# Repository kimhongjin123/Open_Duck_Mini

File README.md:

# Open Duck Mini v2

<table>
  <tr>
    <td> </td>
    <td> </td>
    <td> </td>
   </tr> 
</table>

## Fork addition: MiniDuck IO Shield

This fork adds a custom Raspberry Pi Zero 2 W I/O shield designed for the Open Duck Mini prototype. The addition includes the complete KiCad 9 project, connector and GPIO mapping, BOM, schematic PDF, prototype manufacturing outputs, photos, and a hardware demonstration video.

**[Open the MiniDuck IO Shield documentation](hardware/miniduck-io-shield/README.md)**

> [!IMPORTANT]
> This shield is a community hardware addition maintained in this fork; it is not part of the upstream Open Duck Mini design. Review the documented prototype warnings before fabrication.

We are making a miniature version of the BDX Droid by Disney. It is about 42 centimeters tall with its legs extended.
The full BOM cost should be under $400 !

This repo is kind of a hub where we centralize all resources related to this project. This is a working repo, so there are a lot of undocumented scripts :) We'll try to clean things up at some point.

# State of sim2real

https://github.com/user-attachments/assets/58721d0f-2f95-4088-8900-a5d02f41bba7

https://github.com/user-attachments/assets/4129974a-9d97-4651-9474-c078043bb182

https://github.com/user-attachments/assets/a0afcd38-15d8-40c6-8171-a619107406b8

# Updates

> Update 02/04/2024: You can try two policies we trained : [this one](BEST_WALK_ONNX.onnx) and [this one](BEST_WALK_ONNX_2.onnx)
> Run with the following arguments :
> python v2_rl_walk_mujoco.py --onnx_model_path ~/BEST_WALK_ONNX_2.onnx

> Update 15/03/2025: join our discord server to get help or show us your duck :) https://discord.gg/UtJZsgfQGe

> Update 07/02/2025: Big progress on sim2real, see videos above :)

> Update 24/02/2025: Working hard on sim2real ! 

> Update 07/02/2025 : We are writing documentation on the go, but the design and BOM should not change drastically. Still missing the "expression" features, but they can be added after building the robot!

> Update 22/01/2025 : The mechanical design is pretty much finalized (fixing some mistakes here and there). The current version does not include all the "expression" features we want to include in the final robot (LEDs for the eyes, a camera, a speaker and a microphone). We are now working on making it walk with reinforcement learning !

# Community 

Join our discord community ! https://discord.gg/UtJZsgfQGe

# CAD

https://cad.onshape.com/documents/64074dfcfa379b37d8a47762/w/3650ab4221e215a4f65eb7fe/e/0505c262d882183a25049d05

See [this document](docs/prepare_robot.md) for getting from a onshape design to a simulated robot in MuJoCo (Warning, outdated. Has not been updated in a while)

# RL stuff

We are switching to Mujoco Playground, see this [repo](https://github.com/apirrone/Open_Duck_Playground)

https://github.com/user-attachments/assets/037a1790-7ac1-4140-b154-2c901d20d5f5

## Reference motion generation for imitation learning 

https://github.com/user-attachments/assets/4cb52e17-99a5-47a8-b841-4141596b7afb

See [this repo](https://github.com/apirrone/Open_Duck_reference_motion_generator)

## Actuator identification 

We used Rhoban's [BAM](https://github.com/Rhoban/bam)

# BOM

https://docs.google.com/spreadsheets/d/1gq4iWWHEJVgAA_eemkTEsshXqrYlFxXAPwO515KpCJc/edit?usp=sharing

Chinese: https://zihao-ai.feishu.cn/wiki/AfAtw69vRigXaRk5UkbcrAiLnJw?from=from_copylink

# Build Guide

> New : you can now use the Tnkr guide ! https://tnkr.ai/explore/docs/open-duck-mini/open-duck-mini-v2#home

Chinese: https://zihao-ai.feishu.cn/wiki/space/7488517034406625281

## Print Guide

See [print_guide](docs/print_guide.md).

## Assembly Guide

See [assembly guide (incomplete)](docs/assembly_guide.md).

# Embedded runtime

This repo contains the code to run the policies on the onboard computer (Raspberry pi zero 2w) https://github.com/apirrone/Open_Duck_Mini_Runtime

# Training your own policies

If you want to train your own policies, and contribute to making the ducks walk nicely, see [this document](docs/sim2real.md)

> Thanks a lot to HuggingFace and Pollen Robotics for sponsoring this project !

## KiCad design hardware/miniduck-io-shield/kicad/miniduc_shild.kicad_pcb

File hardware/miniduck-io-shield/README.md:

# MiniDuck IO Shield

A two-layer Raspberry Pi Zero 2 W shield that consolidates power distribution and the Open Duck Mini prototype's servo, foot-switch, IMU, speaker, UART, and LED connections.

This is a fork-specific community hardware addition, designed by KHJ and kept separate from the upstream Open Duck Mini design. The board has been fabricated, assembled with a Raspberry Pi Zero 2 W, and exercised on the robot prototype shown below.

The linked demonstration is a 46.9-second, 1080 x 1920 HEVC MP4. A [five-frame contact sheet](media/hardware-demo-contact-sheet.jpg) is also available for quick viewing.

## Board summary

| Item | Detail |
| --- | --- |
| Controller | Raspberry Pi Zero 2 W, 40-pin GPIO header |
| PCB | 2 layers, 1.6 mm nominal thickness |
| Outline | Approximately 56.0 x 76.5 mm bounding box |
| Input power | 5 V barrel-jack input through onboard slide switch |
| Power outputs | 5 V and 3.3 V screw-terminal breakouts |
| Robot I/O | 2 servo, 2 foot-switch, I2C IMU, I2S speaker, UART, and 3 LED outputs |
| Main connector families | 2.50 mm Molex SPOX, 3.50 mm screw terminals, 2.54 mm pin/IDC headers |
| Design tool | KiCad 9; outputs regenerated with KiCad 9.0.4 |
| Status | Fabricated and assembled prototype; see validation notes before reuse |

## Repository contents

| Path | Contents |
| --- | --- |
| [`kicad/`](kicad/) | Editable schematic, PCB, and project files |
| [`CONNECTORS.md`](CONNECTORS.md) | Connector pinout and Raspberry Pi GPIO mapping |
| [`docs/bom.csv`](docs/bom.csv) | BOM exported from the schematic |
| [`docs/schematic.pdf`](docs/schematic.pdf) | Single-page schematic for quick review |
| [`docs/drc-report.json`](docs/drc-report.json) | KiCad PCB rule-check report |
| [`docs/erc-report.json`](docs/erc-report.json) | KiCad schematic rule-check report |
| [`manufacturing/`](manufacturing/) | Prototype Gerbers, drill files, maps, and a vendor-upload ZIP |
| [`media/`](media/) | Renders, PCB/layout photos, assembly photos, robot photo, and demo video |

The original KiCad basename, `miniduc_shild`, is preserved so the project opens without disrupting its existing file relationships. Local KiCad state, caches, and automatic backups are intentionally excluded.

## Photos

| Fabricated board | Assembled shield |
| --- | --- |
|  |  |

| PCB layout | Robot prototype |
| --- | --- |
|  |  |

## Important prototype notes

- The three LED connector silkscreen labels do not match the electrical nets. Follow the actual-net mapping in [`CONNECTORS.md`](CONNECTORS.md), not the nearby label alone.
- KiCad reports no error-severity ERC/DRC items, but it does report warnings. The exact counts and categories are recorded in [`VALIDATION.md`](VALIDATION.md).
- R1 is a 10 kOhm resistor assigned to a `C_0603_1608Metric` library footprint. The land pattern is 0603-sized, but the library assignment should be corrected in a future revision.
- The custom slide-switch footprint name may not exist in another user's local library. Its placed footprint geometry is embedded in the PCB file.
- The manufacturing package is a reproducible snapshot of this fabricated prototype, not a claim that the design has passed an independent production review.

## Opening and regenerating

1. Open `kicad/miniduc_shild.kicad_pro` in KiCad 9.
2. Review the schematic and PCB against the intended wiring and connector orientation.
3. Run ERC and DRC locally and inspect every warning.
4. Regenerate Gerbers and drill files from the reviewed PCB before ordering a revised batch.

This folder follows the repository's root [Apache-2.0 license](../../LICENSE).

## 한국어 요약

이 폴더는 Raspberry Pi Zero 2 W 기반 Open Duck Mini용 I/O 실드보드 작업을 정리한 것입니다. KiCad 원본, 핀맵, BOM, 회로도 PDF, 시제품 제조 파일, 제작·조립 사진과 구동 영상을 포함합니다. 현재 파일은 실제 제작된 프로토타입 기록이며, LED 커넥터 실크 인쇄와 실제 GPIO 연결이 서로 다르므로 재사용하거나 재발주하기 전에 반드시 [`CONNECTORS.md`](CONNECTORS.md)와 [`VALIDATION.md`](VALIDATION.md)를 확인해야 합니다.

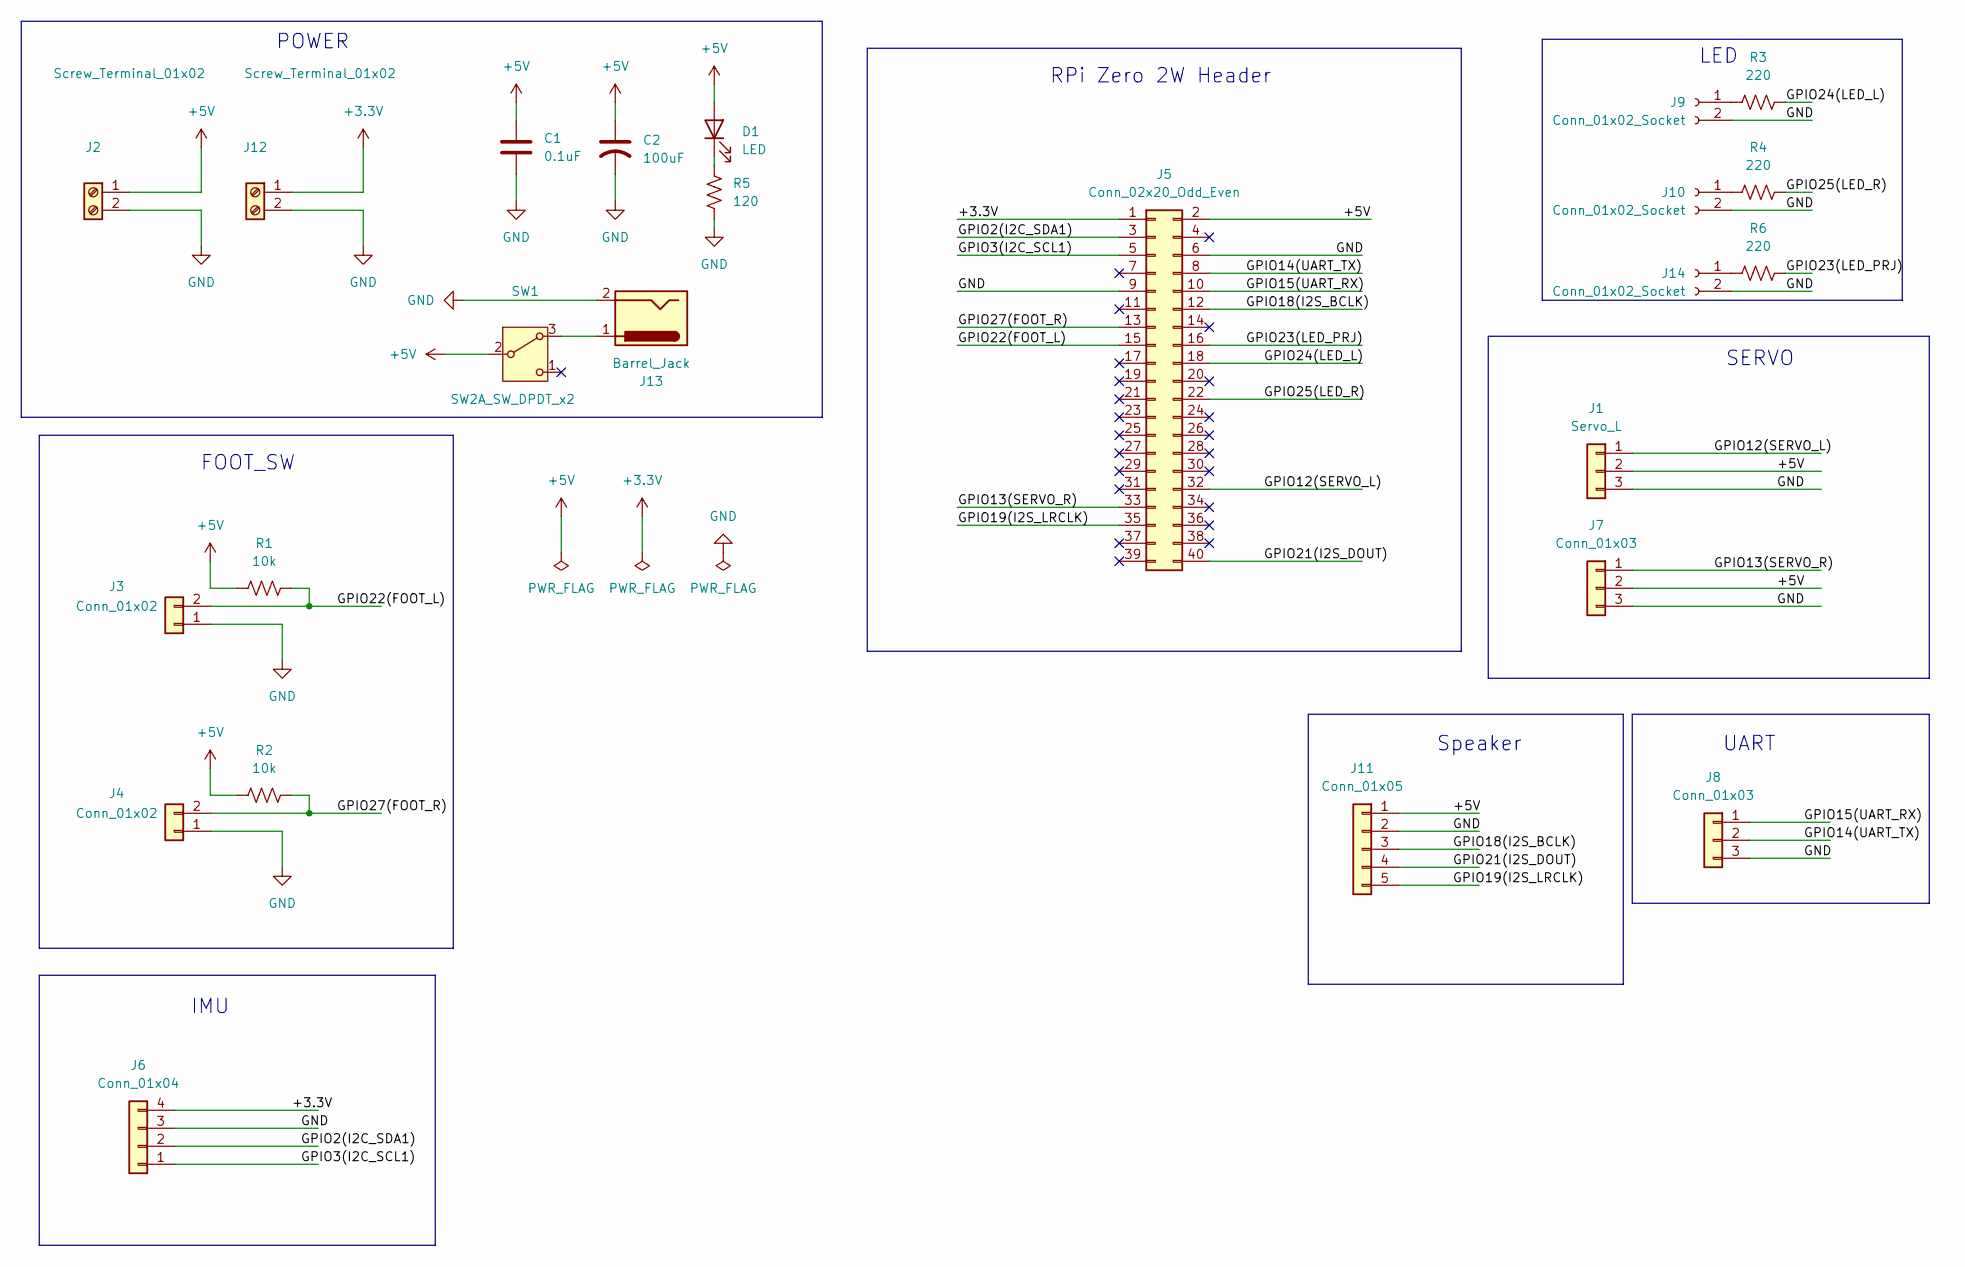
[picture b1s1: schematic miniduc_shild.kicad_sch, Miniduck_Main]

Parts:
C1: 0.1uF; C_0603_1608Metric
C2: 100uF; CP_Elec_6.3x5.3
D1: LED; LED_0603_1608Metric
J1: Servo_L; Molex_SPOX_5267-03A_1x03_P2.50mm_Vertical
J2, J12: Screw_Terminal_01x02; TerminalBlock_4Ucon_1x02_P3.50mm_Horizontal
J3, J4: Conn_01x02; Molex_SPOX_5267-02A_1x02_P2.50mm_Vertical
J5: Conn_02x20_Odd_Even; IDC-Header_2x20_P2.54mm_Latch6.5mm_Vertical
J6: Conn_01x04; Molex_SPOX_5267-04A_1x04_P2.50mm_Vertical
J7: Conn_01x03; Molex_SPOX_5267-03A_1x03_P2.50mm_Vertical
J8: Conn_01x03; PinHeader_1x03_P2.54mm_Vertical
J9, J10, J14: Conn_01x02_Socket; Molex_SPOX_5267-02A_1x02_P2.50mm_Vertical
J11: Conn_01x05; Molex_SPOX_5267-05A_1x05_P2.50mm_Vertical
J13: Barrel_Jack; BarrelJack_Horizontal
R1: 10k; C_0603_1608Metric
R2: 10k; R_0603_1608Metric
R3, R4, R6: 220; R_0603_1608Metric
R5: 120; R_0603_1608Metric
SW1: SW2A_SW_DPDT_x2; SW_Slide_SPDT_PBS110G

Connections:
+3.3V: J5.1, J6.4, J12.1
+5V: C1.2, C2.1, D1.2 (A), J1.2, J2.1, J5.2, J7.2, J11.1, R1.1, R2.1, SW1.2 (B)
/GPIO2(I2C_SDA1): J5.3, J6.2
/GPIO3(I2C_SCL1): J5.5, J6.1
/GPIO12(SERVO_L): J1.1, J5.32
/GPIO13(SERVO_R): J5.33, J7.1
/GPIO14(UART_TX): J5.8, J8.2
/GPIO15(UART_RX): J5.10, J8.1
/GPIO18(I2S_BCLK): J5.12, J11.3
/GPIO19(I2S_LRCLK): J5.35, J11.5
/GPIO21(I2S_DOUT): J5.40, J11.4
/GPIO22(FOOT_L): J3.2, J5.15, R1.2
/GPIO23(LED_PRJ): J5.16, R6.2
/GPIO24(LED_L): J5.18, R3.2
/GPIO25(LED_R): J5.22, R4.2
/GPIO27(FOOT_R): J4.2, J5.13, R2.2
GND: C1.1, C2.2, J1.3, J2.2, J3.1, J4.1, J5.6, J5.9, J6.3, J7.3, J8.3, J9.2, J10.2, J11.2, J12.2, J13.2, J14.2, R5.2
unnamed: D1.1 (K), R5.1
unnamed: J9.1, R3.1
unnamed: J10.1, R4.1
unnamed: J14.1, R6.1
unnamed: J13.1, SW1.3 (A)

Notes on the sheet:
POWER
UART
RPi Zero 2W Header
FOOT_SW
LED
IMU
SERVO
Speaker

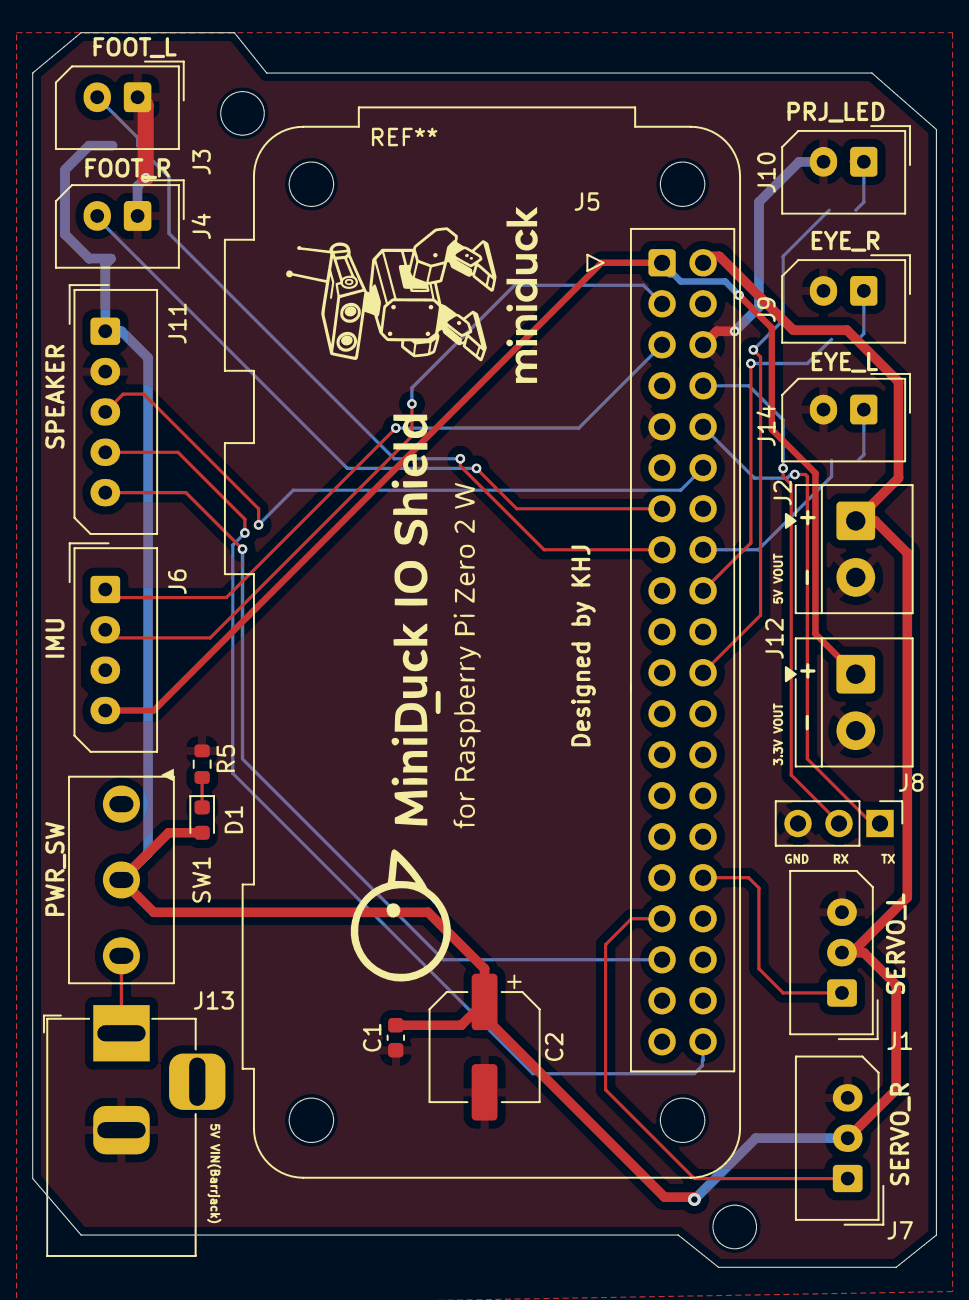
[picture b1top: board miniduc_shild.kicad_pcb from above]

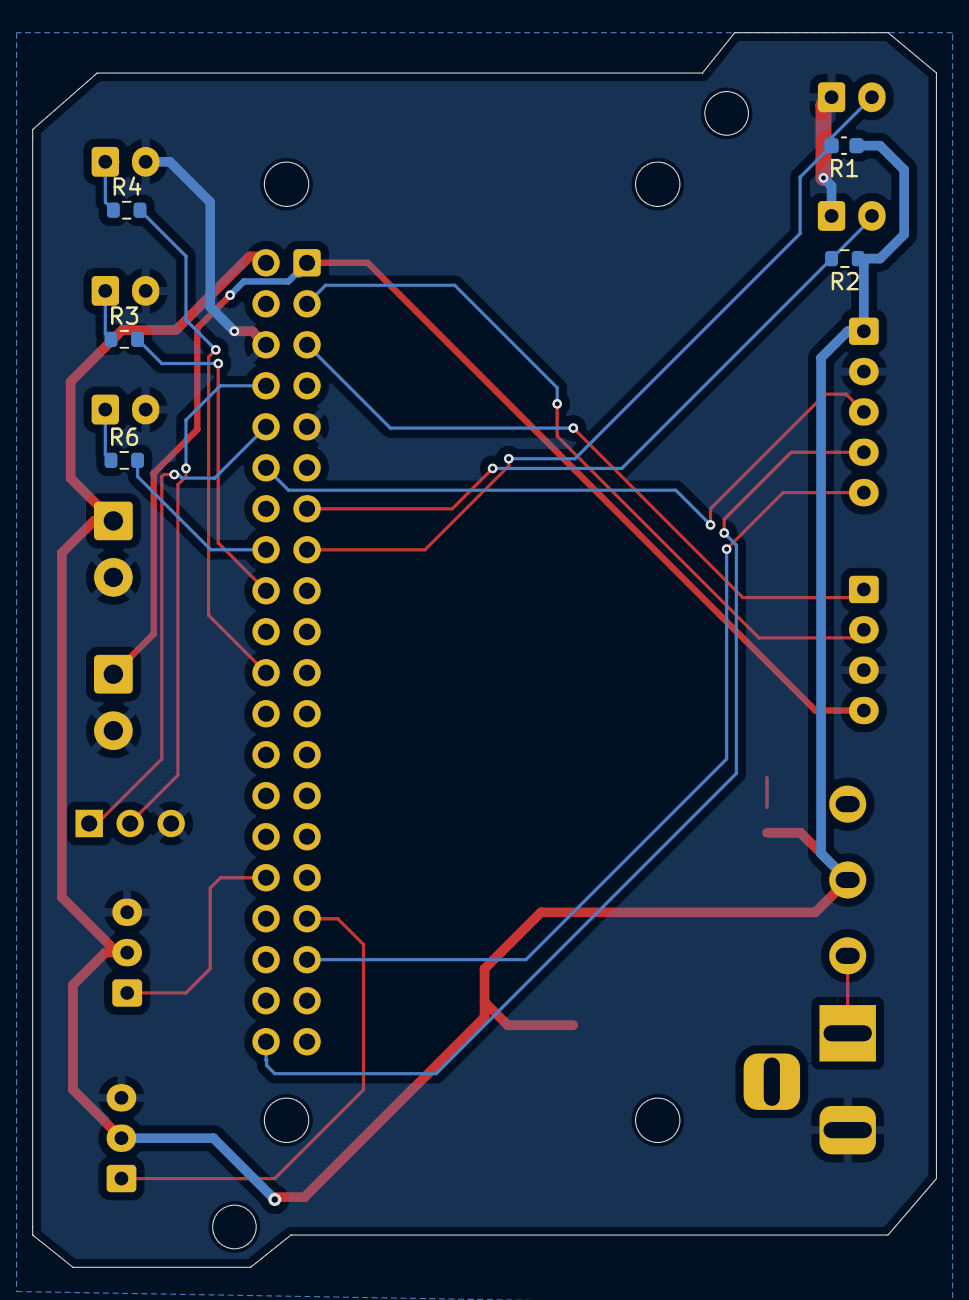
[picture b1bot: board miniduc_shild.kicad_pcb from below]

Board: 2 copper layers, 56.0 x 76.5 mm, 26 parts (5 on the bottom side), 22 nets.

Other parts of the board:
-: LOGO
Designed by KHJ: LOGO

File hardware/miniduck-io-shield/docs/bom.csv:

"Refs","Value","Footprint","Qty","DNP"
"C1","0.1uF","Capacitor_SMD:C_0603_1608Metric","1",""
"C2","100uF","Capacitor_SMD:CP_Elec_6.3x5.3","1",""
"D1","LED","LED_SMD:LED_0603_1608Metric","1",""
"J1","Servo_L","Connector_Molex:Molex_SPOX_5267-03A_1x03_P2.50mm_Vertical","1",""
"J2,J12","Screw_Terminal_01x02","TerminalBlock_4Ucon:TerminalBlock_4Ucon_1x02_P3.50mm_Horizontal","2",""
"J3,J4","Conn_01x02","Connector_Molex:Molex_SPOX_5267-02A_1x02_P2.50mm_Vertical","2",""
"J5","Conn_02x20_Odd_Even","Connector_IDC:IDC-Header_2x20_P2.54mm_Latch6.5mm_Vertical","1",""
"J6","Conn_01x04","Connector_Molex:Molex_SPOX_5267-04A_1x04_P2.50mm_Vertical","1",""
"J7","Conn_01x03","Connector_Molex:Molex_SPOX_5267-03A_1x03_P2.50mm_Vertical","1",""
"J8","Conn_01x03","Connector_PinHeader_2.54mm:PinHeader_1x03_P2.54mm_Vertical","1",""
"J9,J10,J14","Conn_01x02_Socket","Connector_Molex:Molex_SPOX_5267-02A_1x02_P2.50mm_Vertical","3",""
"J11","Conn_01x05","Connector_Molex:Molex_SPOX_5267-05A_1x05_P2.50mm_Vertical","1",""
"J13","Barrel_Jack","Connector_BarrelJack:BarrelJack_Horizontal","1",""
"R1","10k","Capacitor_SMD:C_0603_1608Metric","1",""
"R2","10k","Resistor_SMD:R_0603_1608Metric","1",""
"R3,R4,R6","220","Resistor_SMD:R_0603_1608Metric","3",""
"R5","120","Resistor_SMD:R_0603_1608Metric","1",""
"SW1","SW2A_SW_DPDT_x2","wowmecha:SW_Slide_SPDT_PBS110G","1",""
